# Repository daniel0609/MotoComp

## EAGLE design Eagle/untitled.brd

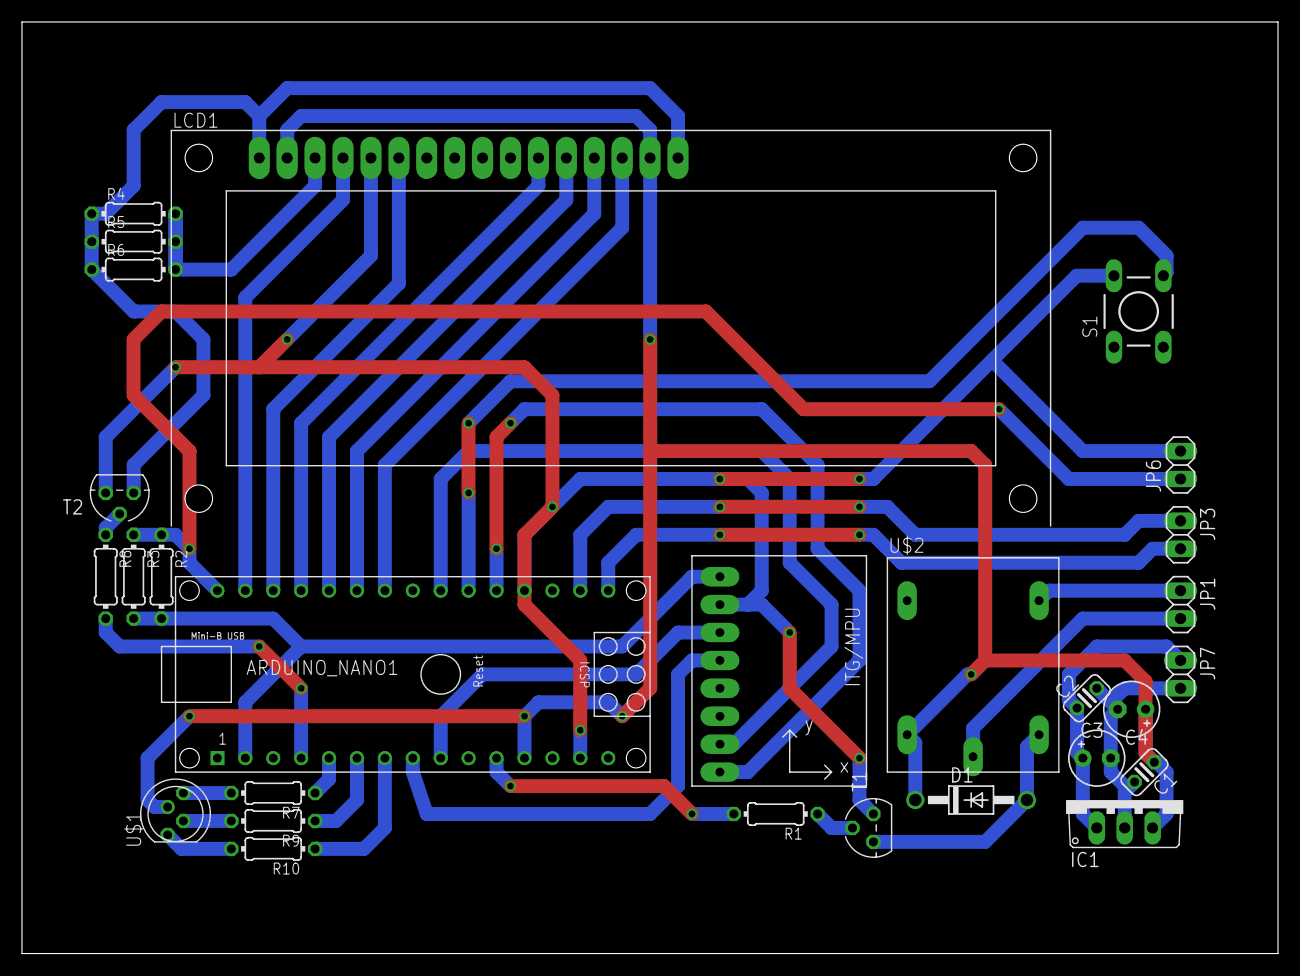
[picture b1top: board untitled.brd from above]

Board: 2 copper layers, 114.3 x 84.8 mm, 28 parts (0 on the bottom side), 32 nets.

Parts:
ARDUINO_NANO1: ARDUINO_NANO
C1, C2: C025-024X044
C3, C4: E2,5-5
D1: 1N4004; DO41-10
IC1: 786TV; TO220V
JP1, JP3, JP6, JP7: 1X02
LCD1: LCD_2X16_SIL; HY-1602F
R1, R2, R3, R4, R5, R6, R7, R8, R9, R10: 0204/7
S1: DTS-6
T1, T2: BC547; TO92
U1: GY-521MPU6050; GY-521
U$1: 5MMRGBLED; LED5MMRGB
U$2: NT73-2A-S12; THT

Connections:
+3V3: ARDUINO_NANO1.2, R2.2, R3.2, U1.VCC
+5V: ARDUINO_NANO1.12, C1.1, C3.+, D1.C, IC1.3, LCD1.2, LCD1.15, U$1.P$3, U$2.1
+12V: C2.1, C4.+, IC1.1, JP1.1, JP7.1, U$2.NO
A0: ARDUINO_NANO1.4, R8.2
A4: ARDUINO_NANO1.8, U1.SDA
A5: ARDUINO_NANO1.9, U1.SCL
A7: ARDUINO_NANO1.11, R1.2
D2: ARDUINO_NANO1.20, U1.INT
D4: ARDUINO_NANO1.22, U1.ADO
D6: ARDUINO_NANO1.24, LCD1.14
D7: ARDUINO_NANO1.25, LCD1.13
D8: ARDUINO_NANO1.26, LCD1.12
D9: ARDUINO_NANO1.27, LCD1.11
D10: ARDUINO_NANO1.28, LCD1.6
D11: ARDUINO_NANO1.29, LCD1.4
GND: ARDUINO_NANO1.14, ARDUINO_NANO1.19, C1.2, C2.2, C3.-, C4.-, IC1.2, JP6.2, JP7.2, LCD1.5, S1.2, T1.1, T2.1, U1.GND
GNDSCREEN: LCD1.1, LCD1.16, R4.1, R5.1, R6.1, T2.3
INT1: ARDUINO_NANO1.21, S1.4
unnamed: D1.A, T1.3, U$2.2
unnamed: R1.1, T1.2
unnamed: JP1.2, U$2.COM
unnamed: LCD1.3, R4.2, R5.2, R6.2
unnamed: R7.2, U$1.P$4
unnamed: R10.2, U$1.P$1
unnamed: ARDUINO_NANO1.6, R9.1
unnamed: ARDUINO_NANO1.5, R7.1
unnamed: R8.1, T2.2
unnamed: ARDUINO_NANO1.16, JP3.2
unnamed: ARDUINO_NANO1.17, JP3.1
unnamed: R9.2, U$1.P$2
unnamed: ARDUINO_NANO1.30, JP6.1, R2.1, R3.1
unnamed: ARDUINO_NANO1.7, R10.1

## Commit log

2017-09-01 git init
